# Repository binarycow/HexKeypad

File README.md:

# HexKeypad

Goal of the project is to make a hex keypad that's similar to 
[IPv6 Buddy](https://www.ipv6buddy.com/), but... better.

- Open source
- Mechanical key switches
- Target use cases
  - IPv4 addresses (Decimal digits, `.`)
  - IPv6 addresses (Hexadecimal digits, `:`)
  - MAC addresses (Hexadecimal digits, `:`, `.`, `-`)
  - Arithmetic (`+`, `-`, `*`, `/`)
  - Misc Keys (Tab, Backspace, Enter)
- No double colon key (`::`) - IPv6 Buddy may have it, but it's silly.
- Big enter key
- Retain the typical keypad layout as much as possible

# License

MIT License.  Do whatever you want with this.  I'm not responsible if 
my schematics are wrong, PCB design is jacked up, or whatever.

# Contributing

You're more than welcome to contribute.  If you test something, and it works out,
I'd love to hear about it.  If you have any suggested changes, please feel free to
file an issue, or open a pull request.

# Next Step

Next step is to test the schematic.  I purchased some buttons [like these](https://p.globalsources.com/IMAGES/PDT/B0979968856/tact-tactile-switch-push-button-switch.jpg),
and I'm going to wire it all up on a breadboard, and make sure the key matrix works the way
I intended.  While I'm at it, I plan on hooking up a microcontroller and testing the firmware
to make sure that it works right.

# Parts

- Key switches
  - 22x 1x1
  - 3x 1x2
- Plate
- PCB
- Microcontroller
  - Shooting for a Teensy 2.0, shouldn't need to upgrade to a Teensy++.
- 3D printed case
- Misc electronics parts (resisters, etc)

# Tasks

- ✔️ **Design layout** 
  - Status: Done
  - [Layout file](Layout/hex-keypad.json)
- ⚠️**Schematic**
  - Status:
    - Complete
    - Not tested
    - Need to wire up a breadboard w/ key switches to test schematic
  - [KiCad Project](Schematics%20and%20PCB/Keyboard/Keyboard.pro)
  - [Schematic File](Schematics%20and%20PCB/Keyboard/Keyboard.sch)
- ⚠️**Firmware**
  - Status:
    - Complete
    - Not tested
    - Need to test after testing the schematics.
  - [Configuration](Firmware/hexkeypad.json)
- ⚠️**PCB**
  - Status:
    - Complete
    - Not tested
    - Need to validate schematic and firmware via breadboard before ordering a prototype board
  - [KiCad Project](Schematics%20and%20PCB/Keyboard/Keyboard.pro)
  - [Schematic File](Schematics%20and%20PCB/Keyboard/Keyboard.kicad_pcb)
- ⚠️**Plate**
  - Status:
    - Completed
    - Not tested
    - Need to validate schematic / PCB before spending any more time/effort on manufacturing/testing.
  - [CAD file](Plate/Keyboard.dxf)
  - [SVG](Plate/Keyboard.svg)
- ❌ **Case**
  - Status:
    - WIP
    - I don't even want to _try_ to "finish" this until the PCB/plate are validated.
  - [Case design](Case/Hex%20Keypad.f3z)

# Tools

- [Keyboard Layout Editor](http://www.keyboard-layout-editor.com/)
- [Keyboard Firmware Builder](https://kbfirmware.com/)
- [KiCad](https://www.kicad.org/)
- [Plate & Case Builder](http://builder.swillkb.com/)
- [Fusion 360](https://www.autodesk.com/products/fusion-360/overview) (free [hobby license](https://www.autodesk.com/products/fusion-360/personal))

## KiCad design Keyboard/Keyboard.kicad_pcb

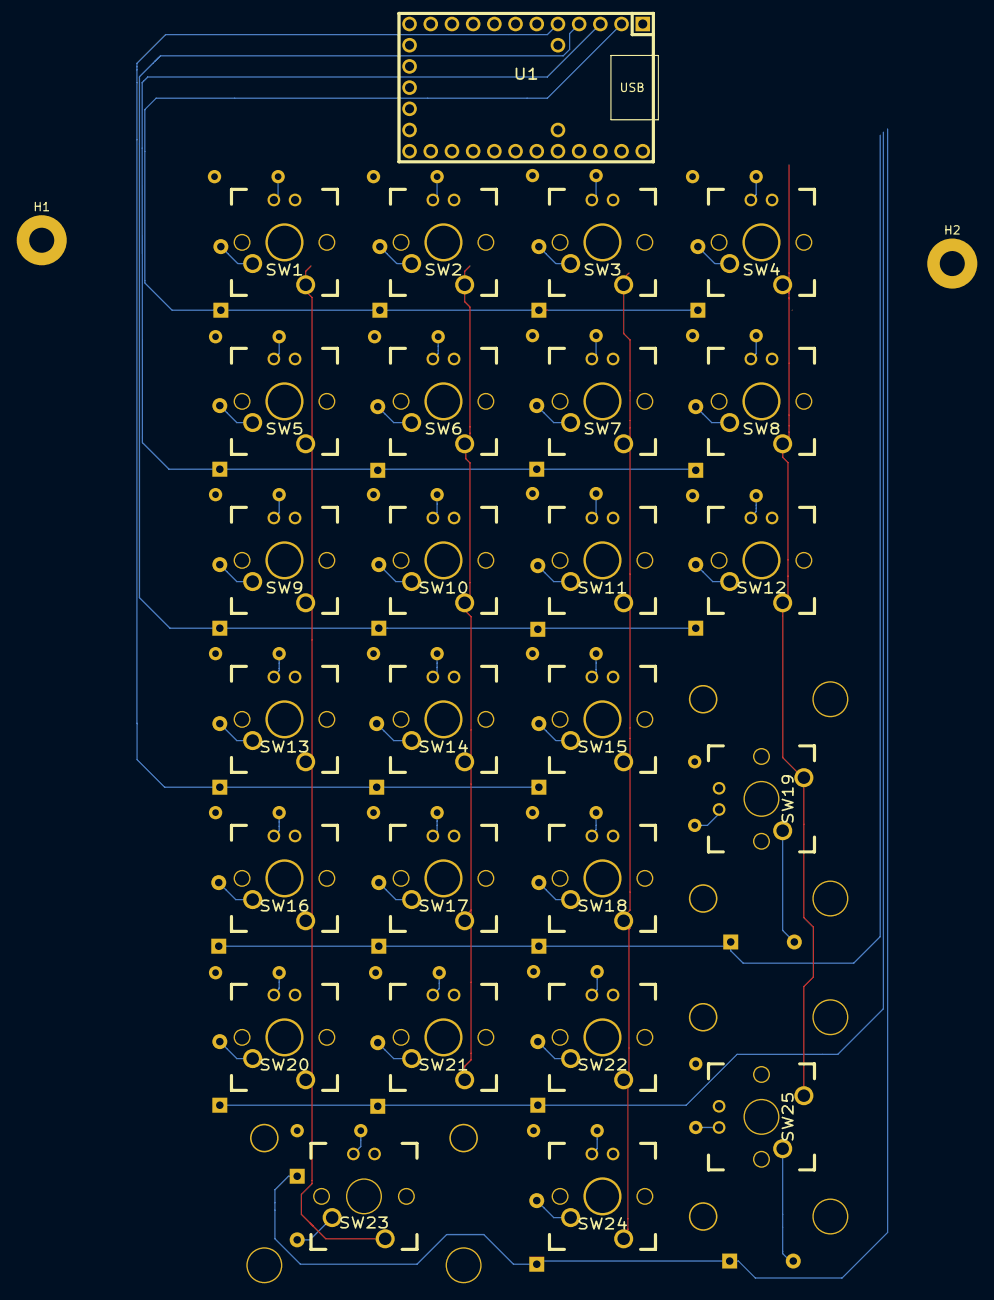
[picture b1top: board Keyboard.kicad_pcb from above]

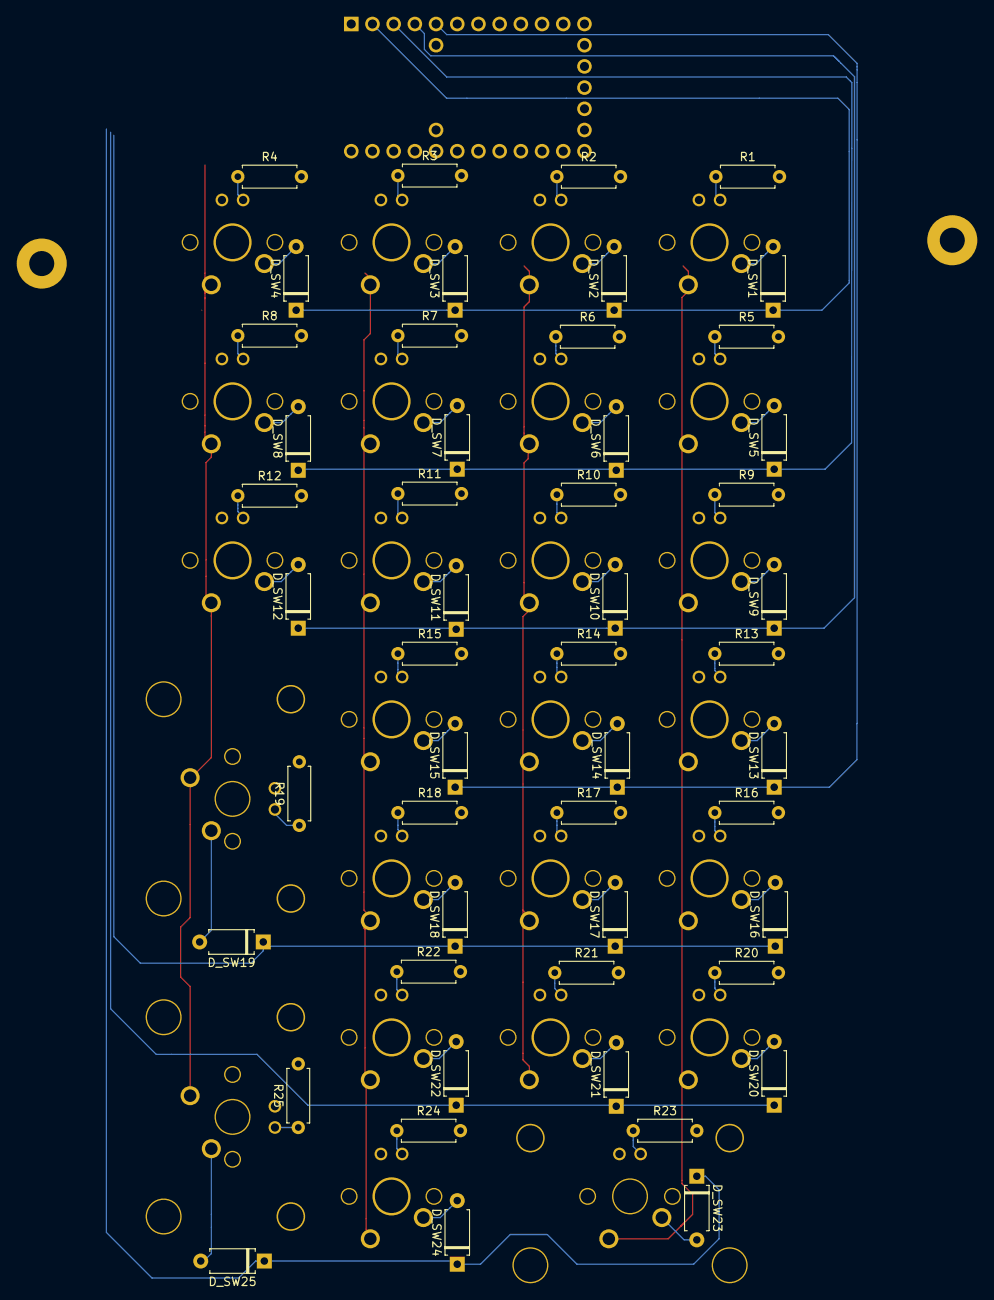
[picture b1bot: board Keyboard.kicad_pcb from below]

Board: 2 copper layers, 78 parts (50 on the bottom side), 63 nets.

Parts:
D_SW1, D_SW2, D_SW3, D_SW4, D_SW5, D_SW6, D_SW7, D_SW8, D_SW9, D_SW10, D_SW11, D_SW12, D_SW13, D_SW14, D_SW15, D_SW16, D_SW17, D_SW18, D_SW19, D_SW20, D_SW21, D_SW22, D_SW23, D_SW24, D_SW25: D_SW; D_A-405_P7.62mm_Horizontal
H1, H2: MountingHole_Pad; MountingHole_3mm_Pad
R1, R2, R3, R4, R5, R6, R7, R8, R9, R10, R11, R12, R13, R14, R15, R16, R17, R18, R19, R20, R21, R22, R23, R24, R25: R220; R_Axial_DIN0207_L6.3mm_D2.5mm_P7.62mm_Horizontal
SW1, SW2, SW3, SW4, SW5, SW6, SW7, SW8, SW9, SW10, SW11, SW12, SW13, SW14, SW15, SW16, SW17, SW18, SW20, SW21, SW22, SW24: MX; CHERRY_PLATE_100H_LED
SW19, SW25: MX; CHERRY_PCB_200V_LED
SW23: MX; CHERRY_PCB_200H_LED
U1: Teensy2.0_(C); TEENSY_2.0

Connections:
Columns0: SW1.1, SW5.1, SW9.1, SW13.1, SW16.1, SW20.1, SW23.1, U1.7
Columns1: SW2.1, SW6.1, SW10.1, SW14.1, SW17.1, SW21.1, U1.8
Columns2: SW3.1, SW7.1, SW11.1, SW15.1, SW18.1, SW22.1, SW24.1, U1.9
Columns3: SW4.1, SW8.1, SW12.1, SW19.1, SW25.1, U1.10
GND: H1.1, H2.1, SW1.3, SW2.3, SW3.3, SW4.3, SW5.3, SW6.3, SW7.3, SW8.3, SW9.3, SW10.3, SW11.3, SW12.3, SW13.3, SW14.3, SW15.3, SW16.3, SW17.3, SW18.3, SW19.3, SW20.3, SW21.3, SW22.3, SW23.3, SW24.3, SW25.3, U1.1, U1.15
LedCol0: R1.2, R2.2, R3.2, R4.2, R5.2, R6.2, R7.2, R8.2, R9.2, R10.2, R11.2, R12.2, R13.2, R14.2, R15.2, R16.2, R17.2, R18.2, R19.2, R20.2, R21.2, R22.2, R23.2, R24.2, R25.2, U1.14, U1.29
unnamed: D_SW1.2, SW1.2
unnamed: D_SW2.2, SW2.2
unnamed: D_SW3.2, SW3.2
unnamed: D_SW4.2, SW4.2
unnamed: D_SW5.2, SW5.2
unnamed: D_SW6.2, SW6.2
unnamed: D_SW7.2, SW7.2
unnamed: D_SW8.2, SW8.2
unnamed: D_SW9.2, SW9.2
unnamed: D_SW10.2, SW10.2
unnamed: D_SW11.2, SW11.2
unnamed: D_SW12.2, SW12.2
unnamed: D_SW13.2, SW13.2
unnamed: D_SW14.2, SW14.2
unnamed: D_SW15.2, SW15.2
unnamed: D_SW16.2, SW16.2
unnamed: D_SW17.2, SW17.2
unnamed: D_SW18.2, SW18.2
unnamed: D_SW19.2, SW19.2
unnamed: D_SW20.2, SW20.2
unnamed: D_SW21.2, SW21.2
unnamed: D_SW22.2, SW22.2
unnamed: D_SW23.2, SW23.2
unnamed: D_SW24.2, SW24.2
unnamed: D_SW25.2, SW25.2
unnamed: R1.1, SW1.4
unnamed: R2.1, SW2.4
unnamed: R3.1, SW3.4
unnamed: R4.1, SW4.4
unnamed: R5.1, SW5.4
unnamed: R6.1, SW6.4
unnamed: R7.1, SW7.4
unnamed: R8.1, SW8.4
unnamed: R9.1, SW9.4
unnamed: R10.1, SW10.4
unnamed: R11.1, SW11.4
unnamed: R12.1, SW12.4
unnamed: R13.1, SW13.4
unnamed: R14.1, SW14.4
unnamed: R15.1, SW15.4
unnamed: R16.1, SW16.4
unnamed: R17.1, SW17.4
unnamed: R18.1, SW18.4
unnamed: R19.1, SW19.4
unnamed: R20.1, SW20.4
unnamed: R21.1, SW21.4
unnamed: R22.1, SW22.4
unnamed: R23.1, SW23.4
unnamed: R24.1, SW24.4
unnamed: R25.1, SW25.4
Rows0: D_SW1.1, D_SW2.1, D_SW3.1, D_SW4.1, U1.2
Rows1: D_SW5.1, D_SW6.1, D_SW7.1, D_SW8.1, U1.3
Rows2: D_SW9.1, D_SW10.1, D_SW11.1, D_SW12.1, U1.4
Rows3: D_SW13.1, D_SW14.1, D_SW15.1, U1.5
Rows4: D_SW16.1, D_SW17.1, D_SW18.1, D_SW19.1, U1.20
Rows5: D_SW20.1, D_SW21.1, D_SW22.1, U1.21
Rows6: D_SW23.1, D_SW24.1, D_SW25.1, U1.22
